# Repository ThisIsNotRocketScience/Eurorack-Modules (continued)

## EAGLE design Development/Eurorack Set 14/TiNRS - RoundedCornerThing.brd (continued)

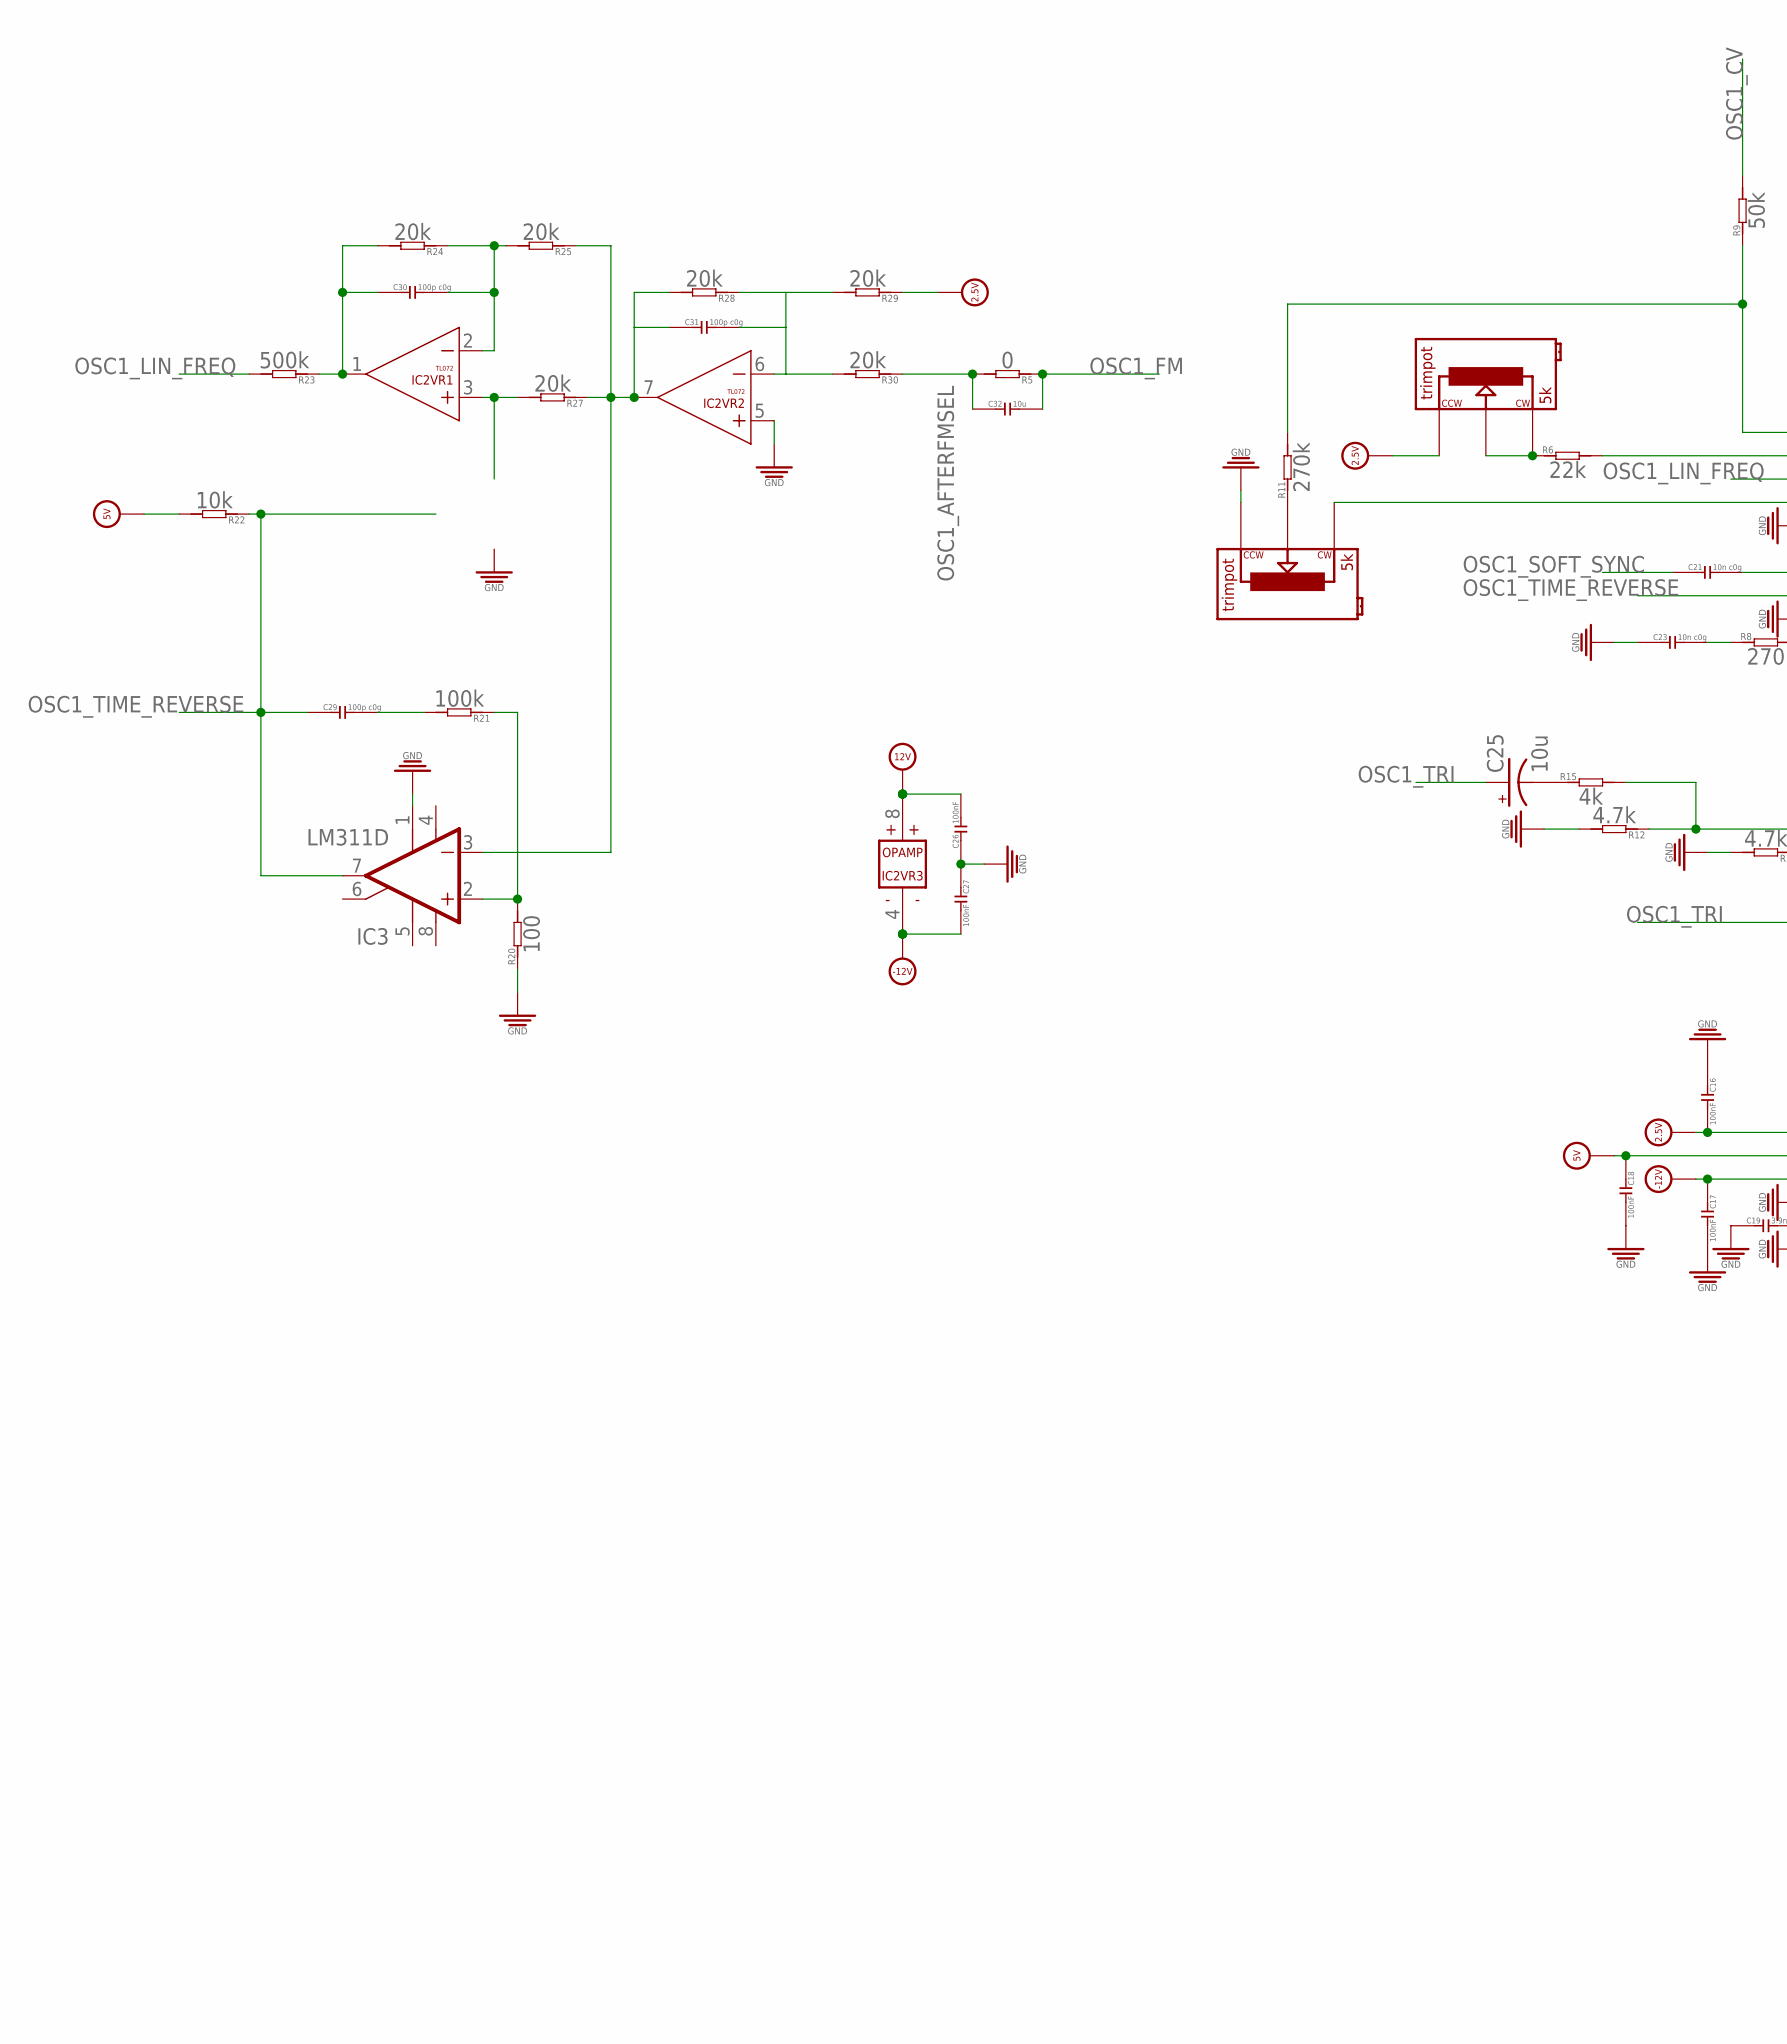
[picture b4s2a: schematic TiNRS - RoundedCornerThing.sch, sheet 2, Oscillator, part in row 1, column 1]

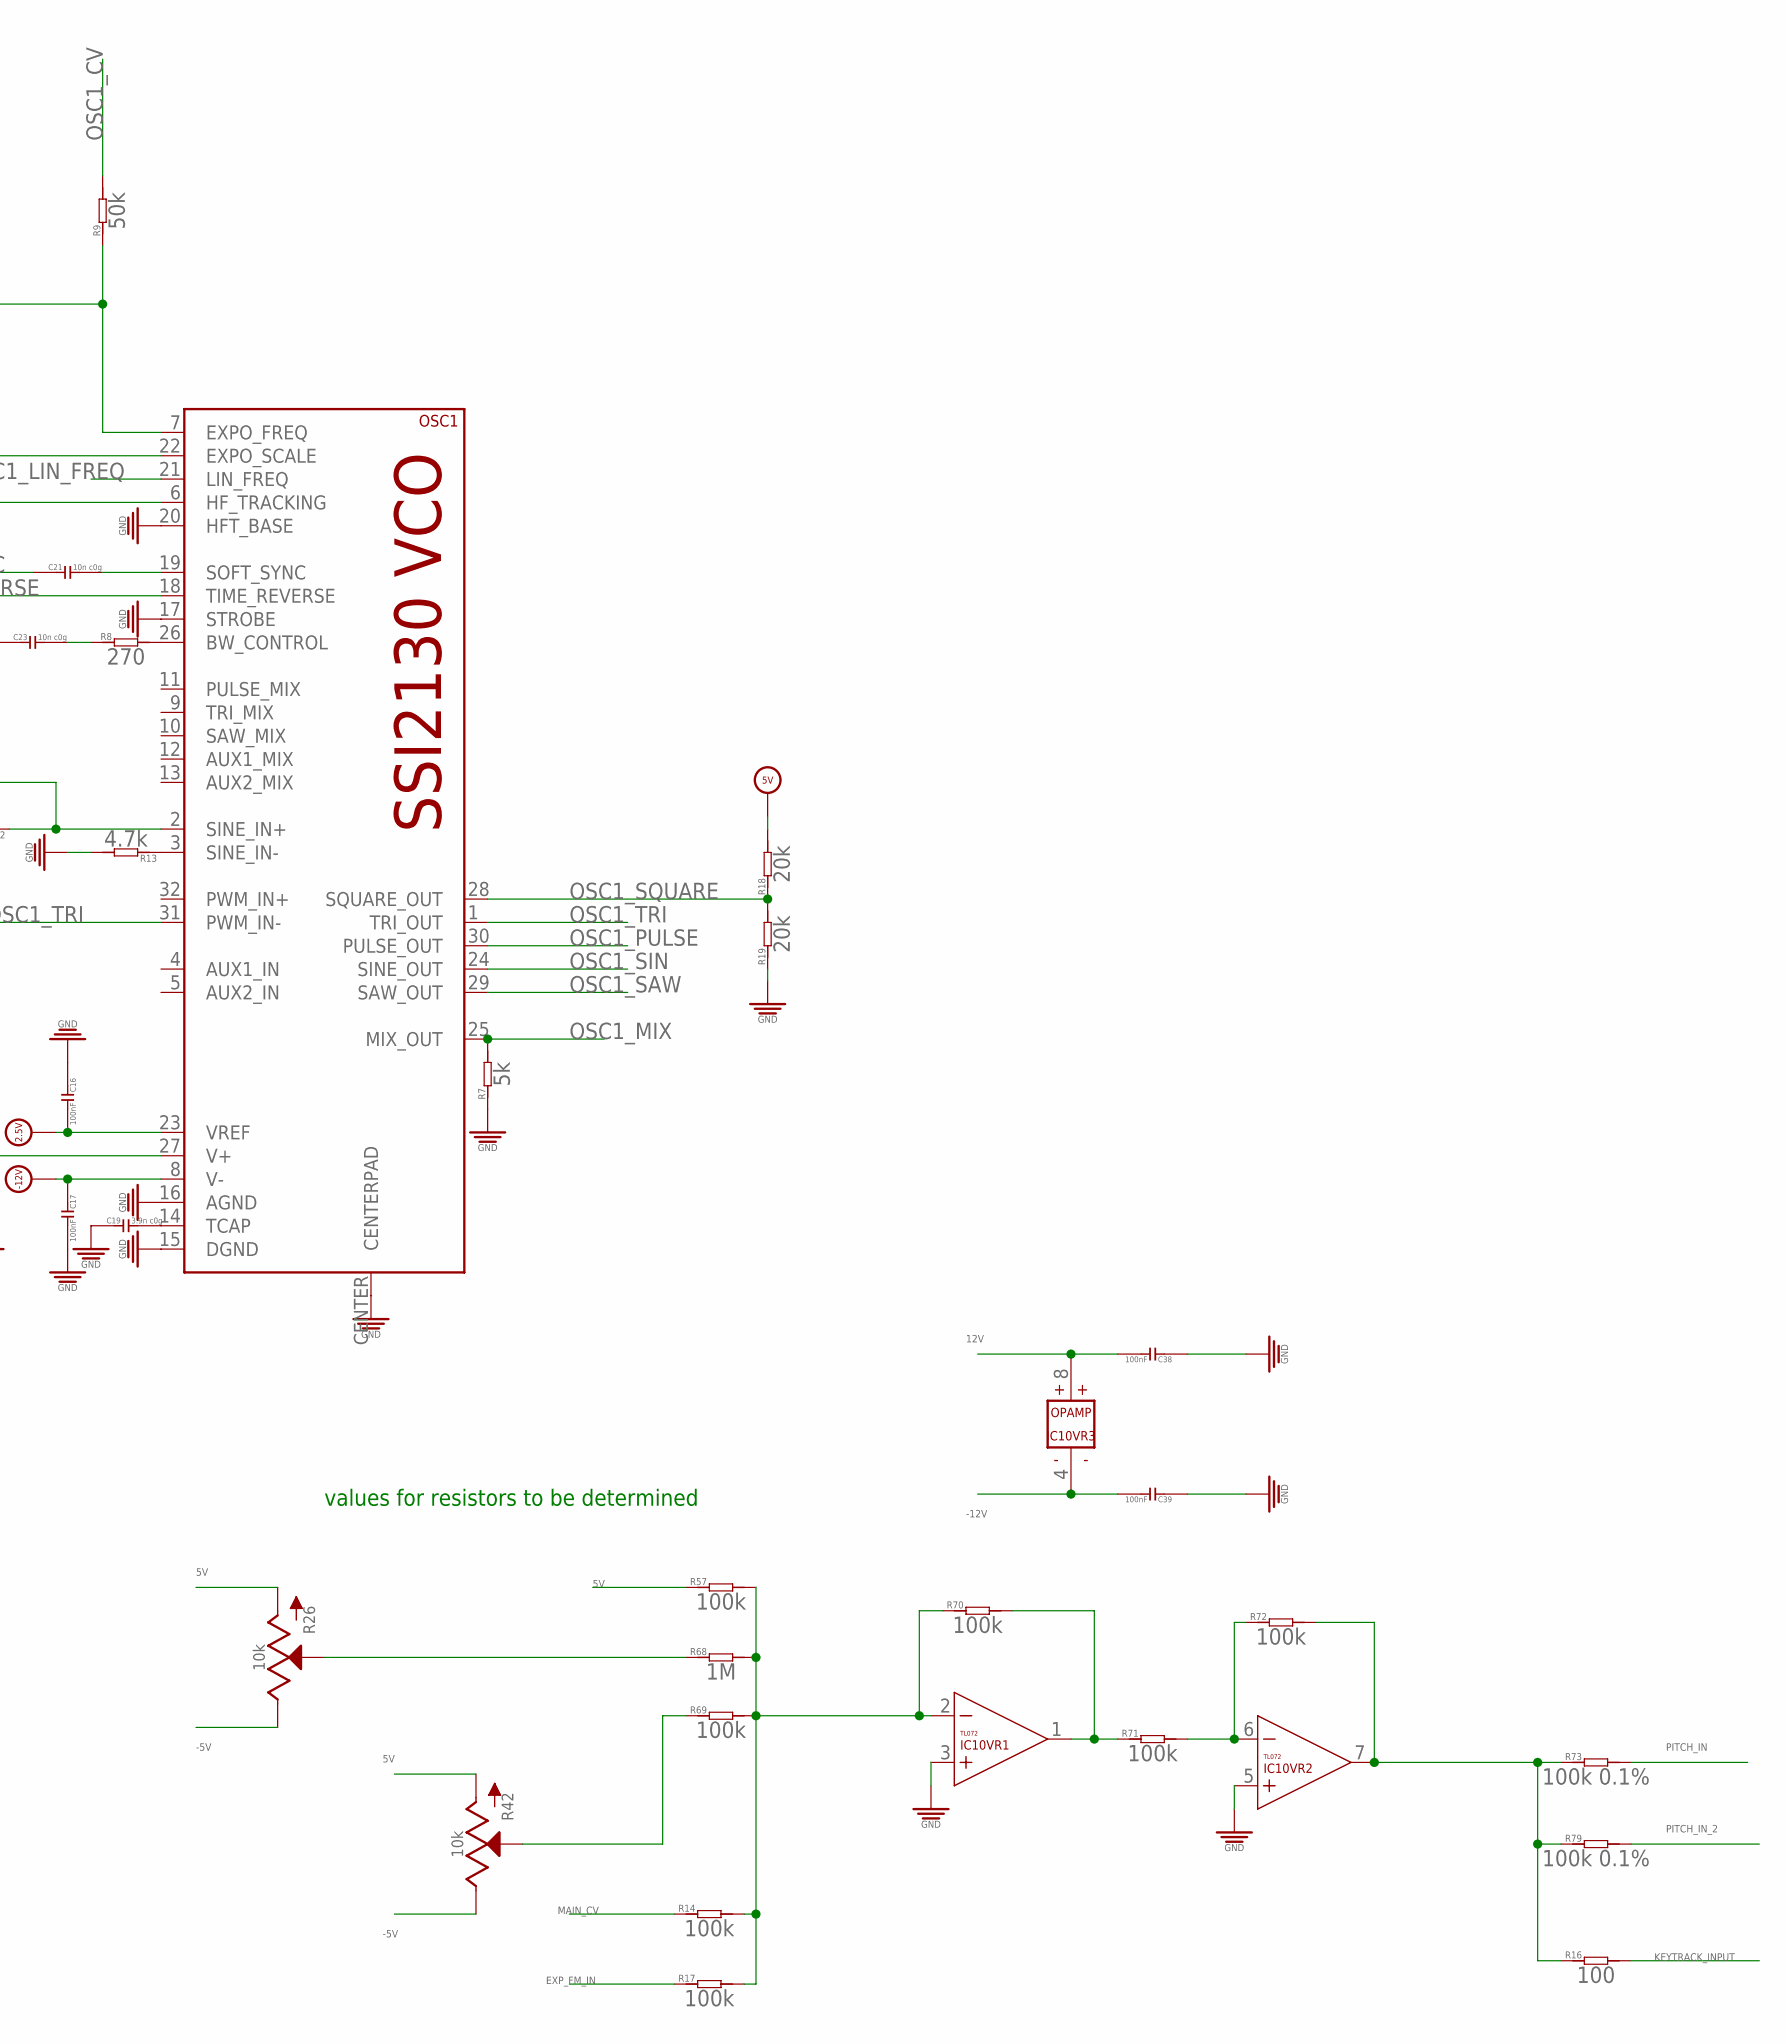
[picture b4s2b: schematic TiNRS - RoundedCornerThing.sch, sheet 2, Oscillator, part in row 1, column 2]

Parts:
C16, C17, C18, C26, C27, C38, C39: 100nF; C0603
C19: 3.9n c0g; C0603
C21, C23: 10n c0g; C0603
C25: 10u; 153CLV-0605
C29, C30, C31: 100p c0g; C0603
C32: 10u; C0603
IC2, IC10: TL072; SO08
IC3: LM311D; SO08
OSC1: SSI2130; QFN32_4X4
R5: 0; R0603
R6: 22k; R0603
R7: 5k; R0603
R8: 270; R0603
R9: 50k; R0603
R10, R189: 5k; TRIMPOT
R11: 270k; R0603
R12, R13: 4.7k; R0603
R14, R17, R21, R57, R69, R70, R71, R72: 100k; R0603
R15: 4k; R0603
R16, R20: 100; R0603
R18, R19, R24, R25, R27, R28, R29, R30: 20k; R0603
R22: 10k; R0603
R23: 500k; R0603
R26, R42: 10k; ALPS_POT_SQUAREHOLES
R68: 1M; R0603
R73, R79: 100k 0.1%; R0603

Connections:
2.5V: C16.2, OSC1.23 (VREF), R29.1, R189.P$1; also elsewhere on the board
5V: C18.1, OSC1.27 (V+), R18.2, R22.2, R26.P$3 (A), R42.P$3 (A), R57.1; also elsewhere on the board
12V: C26.2, C38.2, IC2.8 (V+), IC10.8 (V+); also elsewhere on the board
-5V: R26.P$1 (E), R42.P$1 (E); also elsewhere on the board
-12V: C17.1, C27.2, C39.2, IC2.4 (V-), IC10.4 (V-), OSC1.8 (V-); also elsewhere on the board
EXP_FM_IN: R17.1; also elsewhere on the board
GND: C16.1, C17.2, C18.2, C19.1, C23.1, C26.1, C27.1, C38.1, C39.1, IC2.5 (+IN), IC3.1 (GND), IC10.3 (+IN), IC10.5 (+IN), OSC1.15 (DGND), OSC1.16 (AGND), OSC1.17 (STROBE), OSC1.20 (HFT_BASE), OSC1.CENTER (CENTERPAD), R7.1, R10.P$1, R12.2, R13.2, R19.1, R20.1; also elsewhere on the board
INVERTED_CVSUM: IC10.1 (OUT), R70.2, R71.1
KEYTRACK_INPUT: R16.2; also elsewhere on the board
MAIN_CV: R14.1; also elsewhere on the board
MAIN_CV_SUMLINE: IC10.2 (-IN), R14.2, R17.2, R57.2, R68.2, R69.2, R70.1
MASTER_COARSEPITCH: R42.P$2 (S), R69.1
MASTER_FINEPITCH: R26.P$2 (S), R68.1
unnamed: C19.2, OSC1.14 (TCAP)
unnamed: C21.2, OSC1.19 (SOFT_SYNC)
unnamed: C31.2, IC2.6 (-IN), R30.2
unnamed: OSC1.22 (EXPO_SCALE), R6.2
unnamed: R6.1, R189.P$2, R189.P$3
unnamed: C23.2, R8.1
unnamed: OSC1.26 (BW_CONTROL), R8.2
unnamed: OSC1.7 (EXPO_FREQ), R9.1, R11.2
unnamed: OSC1.6 (HF_TRACKING), R10.P$3
unnamed: R10.P$2, R11.1
unnamed: C25.-, R15.1
unnamed: C30.1, IC2.1 (OUT), R23.1, R24.2
unnamed: OSC1.2 (SINE_IN+), R12.1, R15.2
unnamed: OSC1.3 (SINE_IN-), R13.1
unnamed: C30.2, IC2.2 (-IN), R24.1, R25.2
unnamed: C31.1, IC2.7 (OUT), IC3.3 (-IN), R25.1, R27.1, R28.2
unnamed: IC2.3 (+IN), R27.2
unnamed: R28.1, R29.2
unnamed: IC3.2 (+IN), R20.2, R21.1
unnamed: C29.2, R21.2
OSC1_AFTERFMSEL: C32.1, R5.2, R30.1
OSC1_CV: R9.2
OSC1_FM: C32.2, R5.1
OSC1_LIN_FREQ: OSC1.21 (LIN_FREQ), R23.2
OSC1_MIX: OSC1.25 (MIX_OUT), R7.2
OSC1_PULSE: OSC1.30 (PULSE_OUT)
OSC1_SAW: OSC1.29 (SAW_OUT)
OSC1_SIN: OSC1.24 (SINE_OUT)
OSC1_SOFT_SYNC: C21.1
OSC1_SQUARE: OSC1.28 (SQUARE_OUT), R18.1, R19.2
OSC1_TIME_REVERSE: C29.1, IC3.7 (OUT), OSC1.18 (TIME_REVERSE), R22.1
OSC1_TRI: C25.+, OSC1.1 (TRI_OUT), OSC1.31 (PWM_IN-)
PITCH_IN: R73.2
PITCH_IN_2: R79.2
POSTINVERTED_CVSUM: IC10.6 (-IN), R71.2, R72.1
PRESUMMED_PITCH: IC10.7 (OUT), R16.1, R72.2, R73.1, R79.1
V+: IC3.8 (V+)
V-: IC3.4 (V-)

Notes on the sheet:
values for resistors to be determined

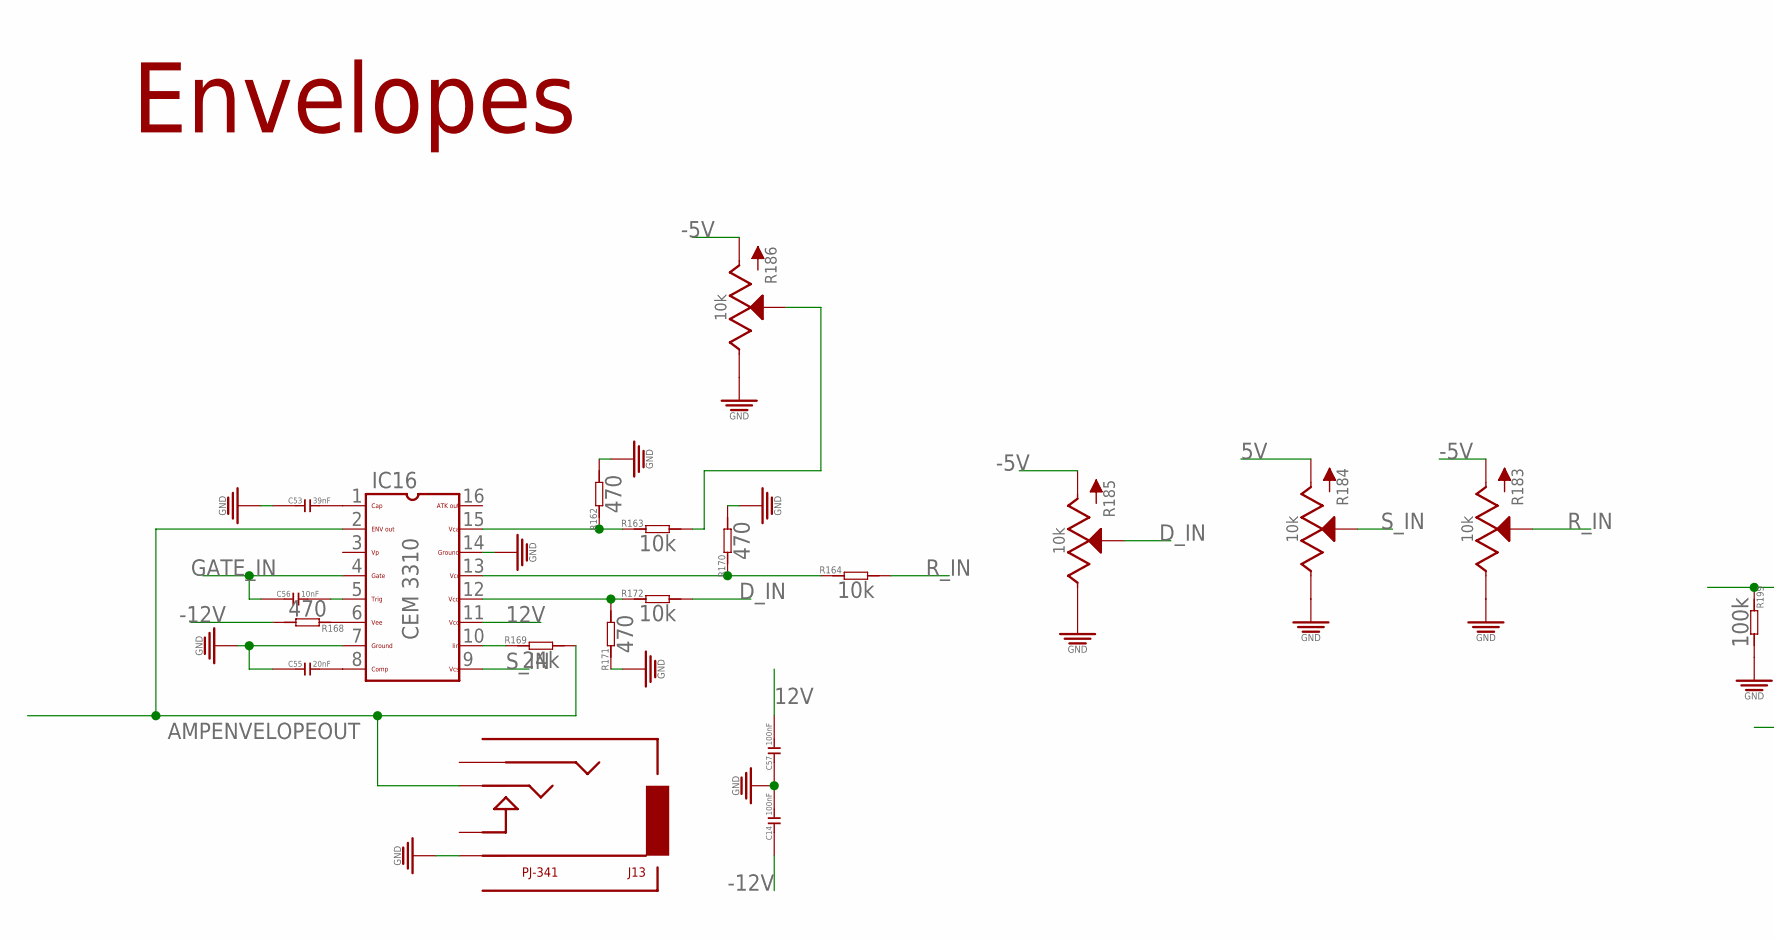
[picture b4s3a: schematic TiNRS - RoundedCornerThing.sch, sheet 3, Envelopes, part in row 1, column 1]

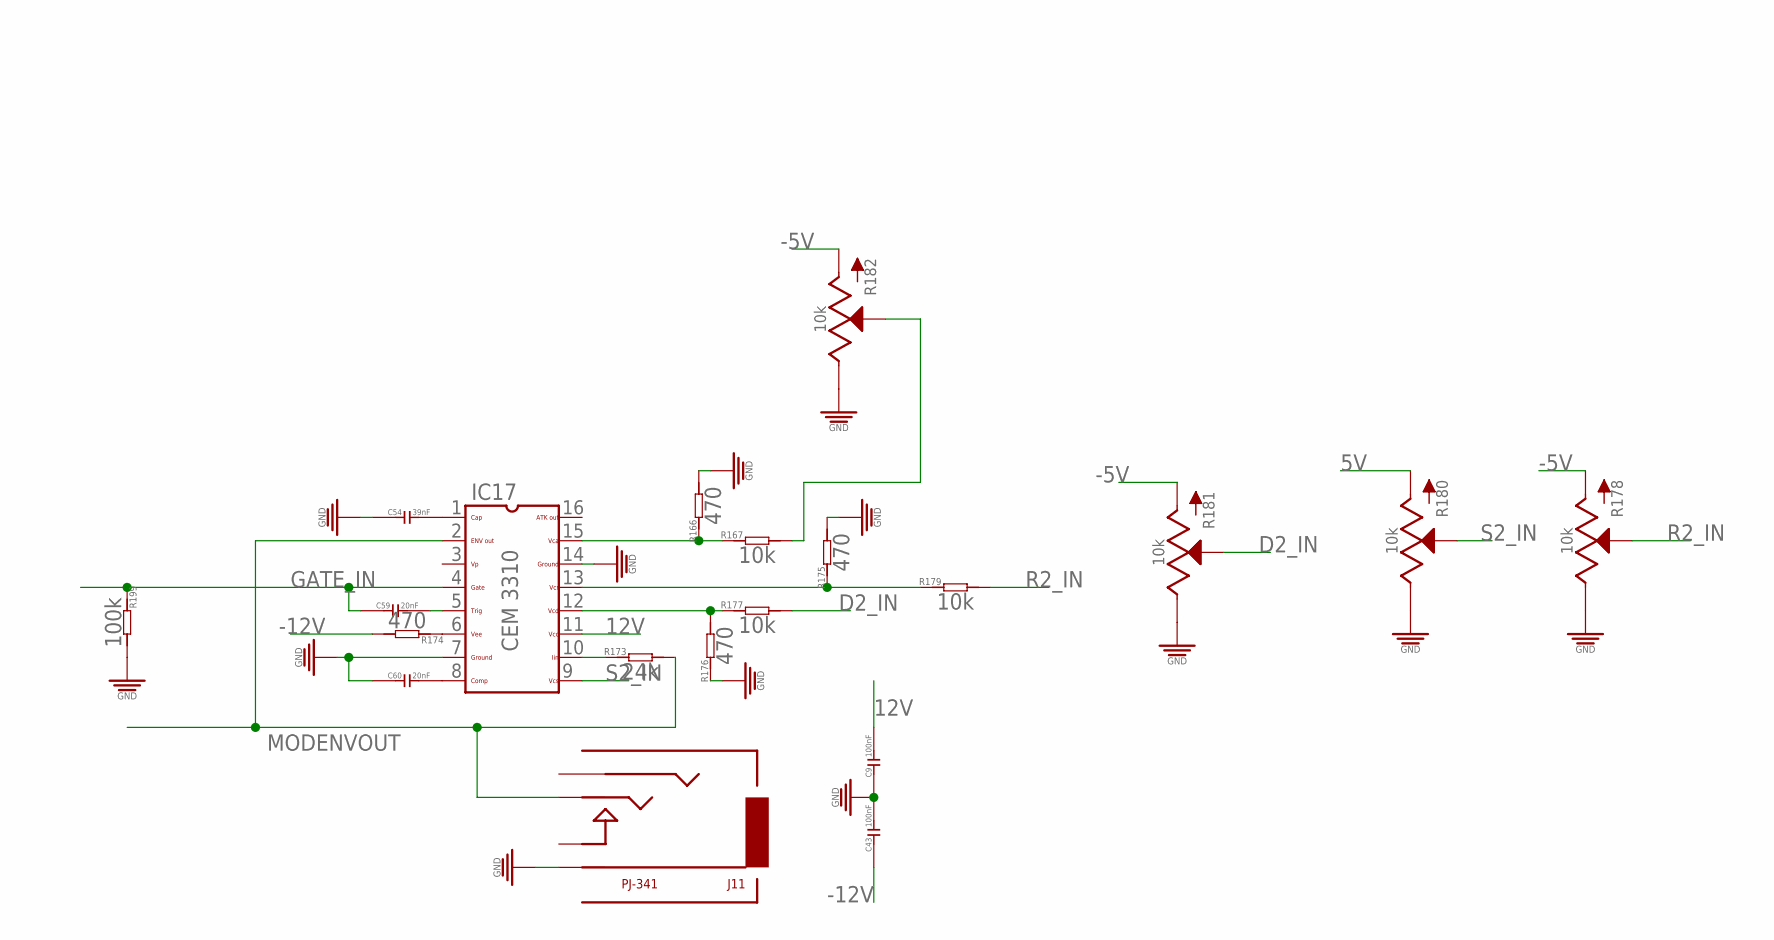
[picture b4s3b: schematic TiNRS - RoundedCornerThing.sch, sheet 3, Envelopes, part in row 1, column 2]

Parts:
C9, C14, C43, C57: 100nF; C0603
C53, C54: 39nF; C0603
C55, C59, C60: 20nF; C0603
C56: 10nF; C0603
IC16, IC17: CEM3310SOIC16; SO16
J11, J13: PJ-341; 3.5MM-JACK-SWITCH-13MM-NOHOLES
R162, R166, R168, R170, R171, R174, R175, R176: 470; R0603
R163, R164, R167, R172, R177, R179: 10k; R0603
R169, R173: 24k; R0603
R178, R180, R181, R182, R183, R184, R185, R186: 10k; ALPS_POT_SQUAREHOLES
R199: 100k; R0603

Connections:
5V: R180.P$3 (A), R184.P$3 (A); also elsewhere on the board
12V: C9.2, C57.2, IC16.11, IC17.11; also elsewhere on the board
-5V: R178.P$3 (A), R181.P$3 (A), R182.P$3 (A), R183.P$3 (A), R185.P$3 (A), R186.P$3 (A); also elsewhere on the board
-12V: C14.1, C43.1, R168.2, R174.2; also elsewhere on the board
A2_IN: R167.2, R182.P$2 (S)
AMPENVELOPEOUT: IC16.2, J13.TIP_B@1 (TIP), J13.TIP_T@3 (TIP), R169.2; also elsewhere on the board
A_IN: R163.2, R186.P$2 (S)
D2_IN: R177.2, R181.P$2 (S)
D_IN: R172.2, R185.P$2 (S)
GATE_IN: C56.1, C59.1, IC16.4, IC17.4, R199.1; also elsewhere on the board
GND: C9.1, C14.2, C43.2, C53.1, C54.1, C55.1, C57.1, C60.1, IC16.7, IC16.14, IC17.7, IC17.14, J11.RING_B@1 (RING), J11.RING_T@3 (RING), J13.RING_B@1 (RING), J13.RING_T@3 (RING), R162.2, R166.2, R170.2, R171.1, R175.2, R176.1, R178.P$1 (E), R180.P$1 (E), R181.P$1 (E), R182.P$1 (E), R183.P$1 (E), R184.P$1 (E), R185.P$1 (E), R186.P$1 (E), R199.2; also elsewhere on the board
MODENVOUT: IC17.2, J11.TIP_B@1 (TIP), J11.TIP_T@3 (TIP), R173.2; also elsewhere on the board
unnamed: IC16.15, R162.1, R163.1
unnamed: IC16.12, R171.2, R172.1
unnamed: IC16.13, R164.1, R170.1
unnamed: C53.2, IC16.1
unnamed: C56.2, IC16.5
unnamed: IC16.6, R168.1
unnamed: C55.2, IC16.8
unnamed: IC16.10, R169.1
unnamed: IC17.15, R166.1, R167.1
unnamed: IC17.12, R176.2, R177.1
unnamed: IC17.13, R175.1, R179.1
unnamed: C59.2, IC17.5
unnamed: IC17.6, R174.1
unnamed: C60.2, IC17.8
unnamed: IC17.10, R173.1
unnamed: C54.2, IC17.1
R2_IN: R178.P$2 (S), R179.2
R_IN: R164.2, R183.P$2 (S)
S2_IN: IC17.9, R180.P$2 (S)
S_IN: IC16.9, R184.P$2 (S)

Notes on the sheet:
Envelopes

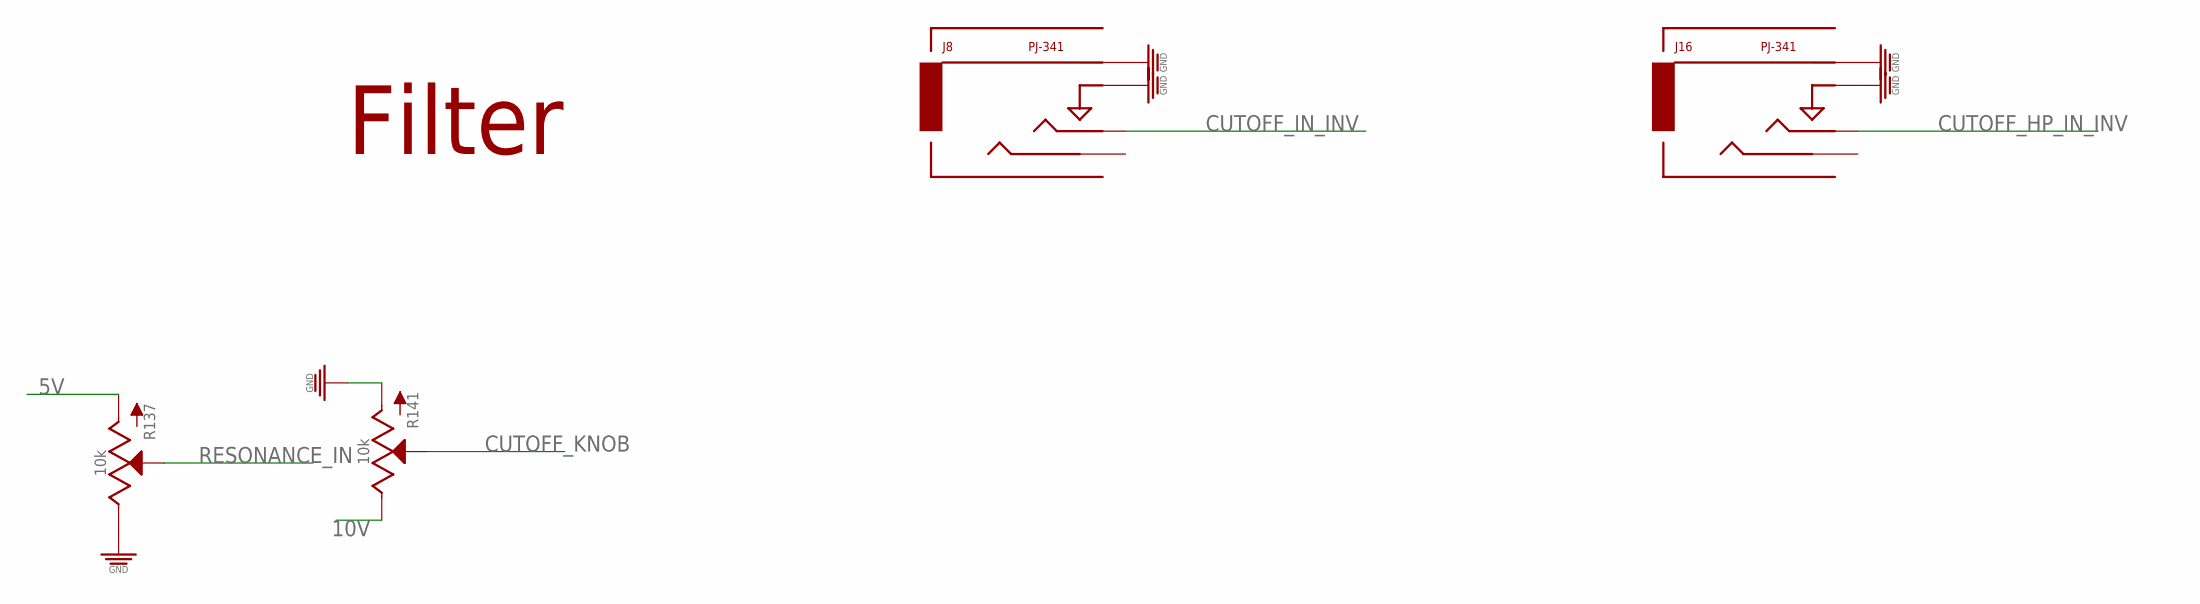
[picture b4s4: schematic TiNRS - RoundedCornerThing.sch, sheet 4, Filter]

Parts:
J8, J16: PJ-341; 3.5MM-JACK-SWITCH-13MM-NOHOLES
R137, R141: 10k; ALPS_POT_SQUAREHOLES

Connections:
5V: R137.P$3 (A); also elsewhere on the board
10V: R141.P$1 (E); also elsewhere on the board
CUTOFF_HP_IN_INV: J16.TIP_B@1 (TIP), J16.TIP_T@3 (TIP); also elsewhere on the board
CUTOFF_IN_INV: J8.TIP_B@1 (TIP), J8.TIP_T@3 (TIP); also elsewhere on the board
CUTOFF_KNOB: R141.P$2 (S)
GND: J8.RING_B@1 (RING), J8.RING_T@3 (RING), J8.SWITCH_B@1 (SWITCH), J8.SWITCH_T@3 (SWITCH), J16.RING_B@1 (RING), J16.RING_T@3 (RING), J16.SWITCH_B@1 (SWITCH), J16.SWITCH_T@3 (SWITCH), R137.P$1 (E), R141.P$3 (A); also elsewhere on the board
RESONANCE_IN: R137.P$2 (S)

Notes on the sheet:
Filter

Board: 2 copper layers, 183 parts (7 on the bottom side), 113 nets, no tracks yet.

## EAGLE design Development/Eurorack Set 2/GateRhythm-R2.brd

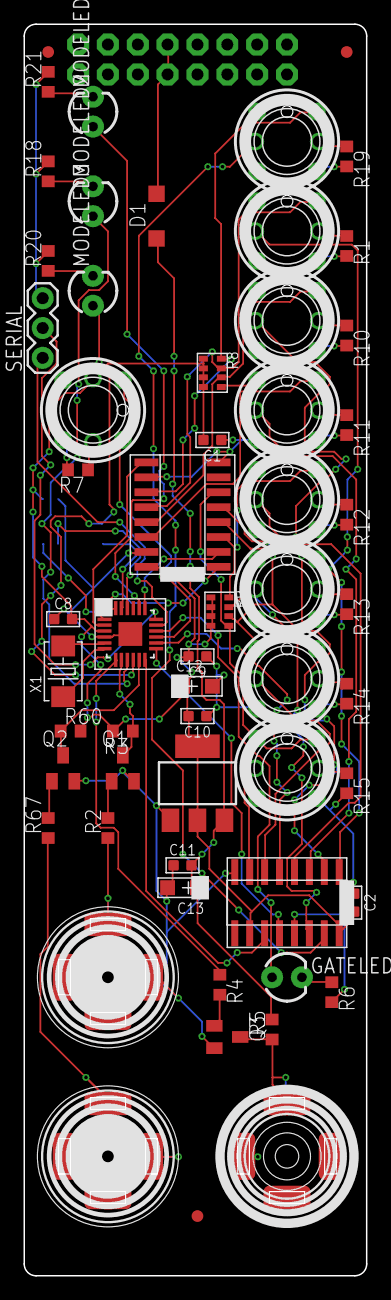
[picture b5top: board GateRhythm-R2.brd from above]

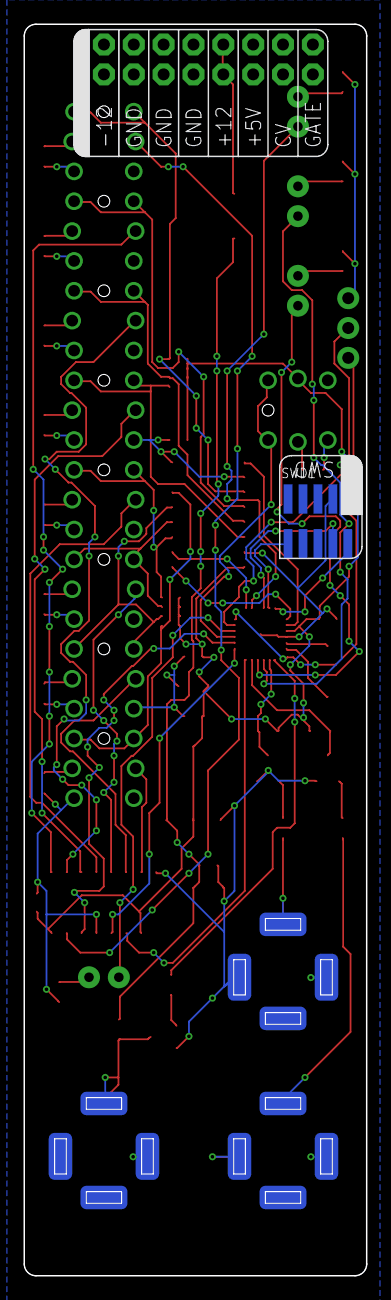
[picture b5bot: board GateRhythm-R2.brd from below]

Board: 2 copper layers, 29.1 x 106.5 mm, 61 parts (2 on the bottom side), 60 nets.

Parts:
B1, B2, B3, B4, B5, B6, B7, B8, B9: SWITCH_W_LED_PB6149L-X-102WHITE; PB6149L
C1, C2, C11: 100Nf; C0603
C8, C10: 100nF; C0603
C9: 1uF; C0603
C12: 10uF; AVX-A
C13: 10Uf; AVX-A
CLOCK: Clock; 3.5MM-JACK-SWITCH-13MM-INPUT
D1: 1N5819HW; SOD123
GATE: Gate; 3.5MM-JACK-SWITCH-13MM-OUTPUT
GATELED: LED3MM
IC1: LD1117AS33TR; SOT223
IC2: IC_74HC595-SOIC-16; SOIC-16
IC3: 74AC165D; SO16
MODELED1, MODELED2, MODELED3: LED3MM
Q1, Q2, Q3: MMBT3904; SOT23-BEC
R1, R6, R7, R10, R11, R12, R13, R14, R15, R18, R19, R20, R21: 120; R0603
R2, R4, R67: 100k; R0603
R3, R5, R60: 10k; R0603
R8, R9: 10k; R1206-8
RESET: Reset; 3.5MM-JACK-SWITCH-13MM-INPUT
SERIAL: 1X03
SWD1: CORTEX_SWD; M50-3600542
U1: MKL02Z32VFK4; QFN50P400X400X100-25N
U$1: POWER; POWER_16
U$2: EURORACK_PCB6HP; EURORACK6HPPCB
U$3, U$4, U$5: FIDUCIAL; FIDUCIAL_1MM
X1: CRYSTAL-0500290P1; 2P-SMD-5.0X3.2

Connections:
3.3V: B9.LEDPOS, C1.2, C2.2, C8.2, C9.2, C10.2, C12.+, IC1.2, IC1.4, IC2.10, IC2.16, IC3.16, R3.2, R8.1, R8.2, R8.3, R8.4, R9.1, R9.2, R9.3, R9.4, R60.2, SWD1.1, U1.3
12V: C11.2, C13.+, D1.C, IC1.3, R5.2
BUTTON1: B1.1, B1.2, IC3.11, R8.8
BUTTON2: B2.1, B2.2, IC3.12, R8.7
BUTTON3: B3.1, B3.2, IC3.13, R8.6
BUTTON4: B4.1, B4.2, IC3.14, R8.5
BUTTON5: B5.1, B5.2, IC3.3, R9.8
BUTTON6: B6.1, B6.2, IC3.4, R9.7
BUTTON7: B7.1, B7.2, IC3.5, R9.6
BUTTON8: B8.1, B8.2, IC3.6, R9.5
BUTTONCLOCK: IC3.2, U1.19
BUTTONDAT: IC3.9, U1.2
BUTTONLATCH: IC3.1, U1.1
CLOCK: Q2.C, R60.1, U1.11
GATELED: GATELED.A, U1.16
GND: B1.3, B1.4, B2.3, B2.4, B3.3, B3.4, B4.3, B4.4, B5.3, B5.4, B6.3, B6.4, B7.3, B7.4, B8.3, B8.4, B9.3, B9.4, C1.1, C2.1, C8.1, C9.1, C10.1, C11.1, C12.-, C13.-, CLOCK.RING@1, CLOCK.RING@2, CLOCK.SWITCH@1, CLOCK.SWITCH@2, GATE.RING@1, GATE.RING@2, IC1.1, IC2.8, IC2.13, IC3.8, IC3.10, IC3.15, Q1.E, Q2.E, Q3.E, R1.2, R6.2, R7.2, R10.2, R11.2, R12.2, R13.2, R14.2, R15.2, R18.2, R19.2, R20.2, R21.2, RESET.RING@1, RESET.RING@2, RESET.SWITCH@1, RESET.SWITCH@2, SERIAL.3, SWD1.3, SWD1.5, U1.4, U1.25, U$1.3, U$1.4, U$1.5, U$1.6, U$1.7, U$1.8
LEDB1: B1.LEDPOS, IC2.15
LEDB2: B2.LEDPOS, IC2.1
LEDB3: B3.LEDPOS, IC2.2
LEDB4: B4.LEDPOS, IC2.3
LEDB5: B5.LEDPOS, IC2.4
LEDB6: B6.LEDPOS, IC2.5
LEDB7: B7.LEDPOS, IC2.6
LEDB8: B8.LEDPOS, IC2.7
LEDCLOCK: IC2.11, U1.12
LEDDAT: IC2.14, U1.14
LEDLATCH: IC2.12, U1.13
MODEBUTTON: B9.1, B9.2, U1.15
MODELED1: MODELED1.A, U1.20
MODELED2: MODELED2.A, U1.9
MODELED3: MODELED3.A, U1.10
unnamed: U1.5, X1.2
unnamed: U1.6, X1.1
unnamed: B2.LEDNEG, R1.1
unnamed: Q1.B, R2.2
unnamed: SWD1.4, U1.22
unnamed: R2.1, RESET.TIP@1, RESET.TIP@2
unnamed: SWD1.2, U1.24
unnamed: B3.LEDNEG, R10.1
unnamed: Q3.B, R4.2
unnamed: GATELED.K, R6.1
unnamed: B9.LEDNEG, R7.1
unnamed: D1.A, U$1.9, U$1.10
unnamed: B1.LEDNEG, R19.1
unnamed: MODELED2.K, R18.1
unnamed: MODELED3.K, R20.1
unnamed: MODELED1.K, R21.1
unnamed: B4.LEDNEG, R11.1
unnamed: B5.LEDNEG, R12.1
unnamed: B6.LEDNEG, R13.1
unnamed: B7.LEDNEG, R14.1
unnamed: B8.LEDNEG, R15.1
unnamed: CLOCK.TIP@1, CLOCK.TIP@2, R67.1
unnamed: Q2.B, R67.2
PTA1: SWD1.10, U1.23
RESET: Q1.C, R3.1, U1.8
RX: SERIAL.2, U1.18
TRIG: R4.1, U1.7
TRIGGEROUT: GATE.TIP@1, GATE.TIP@2, Q3.C, R5.1
TX: SERIAL.1, U1.17

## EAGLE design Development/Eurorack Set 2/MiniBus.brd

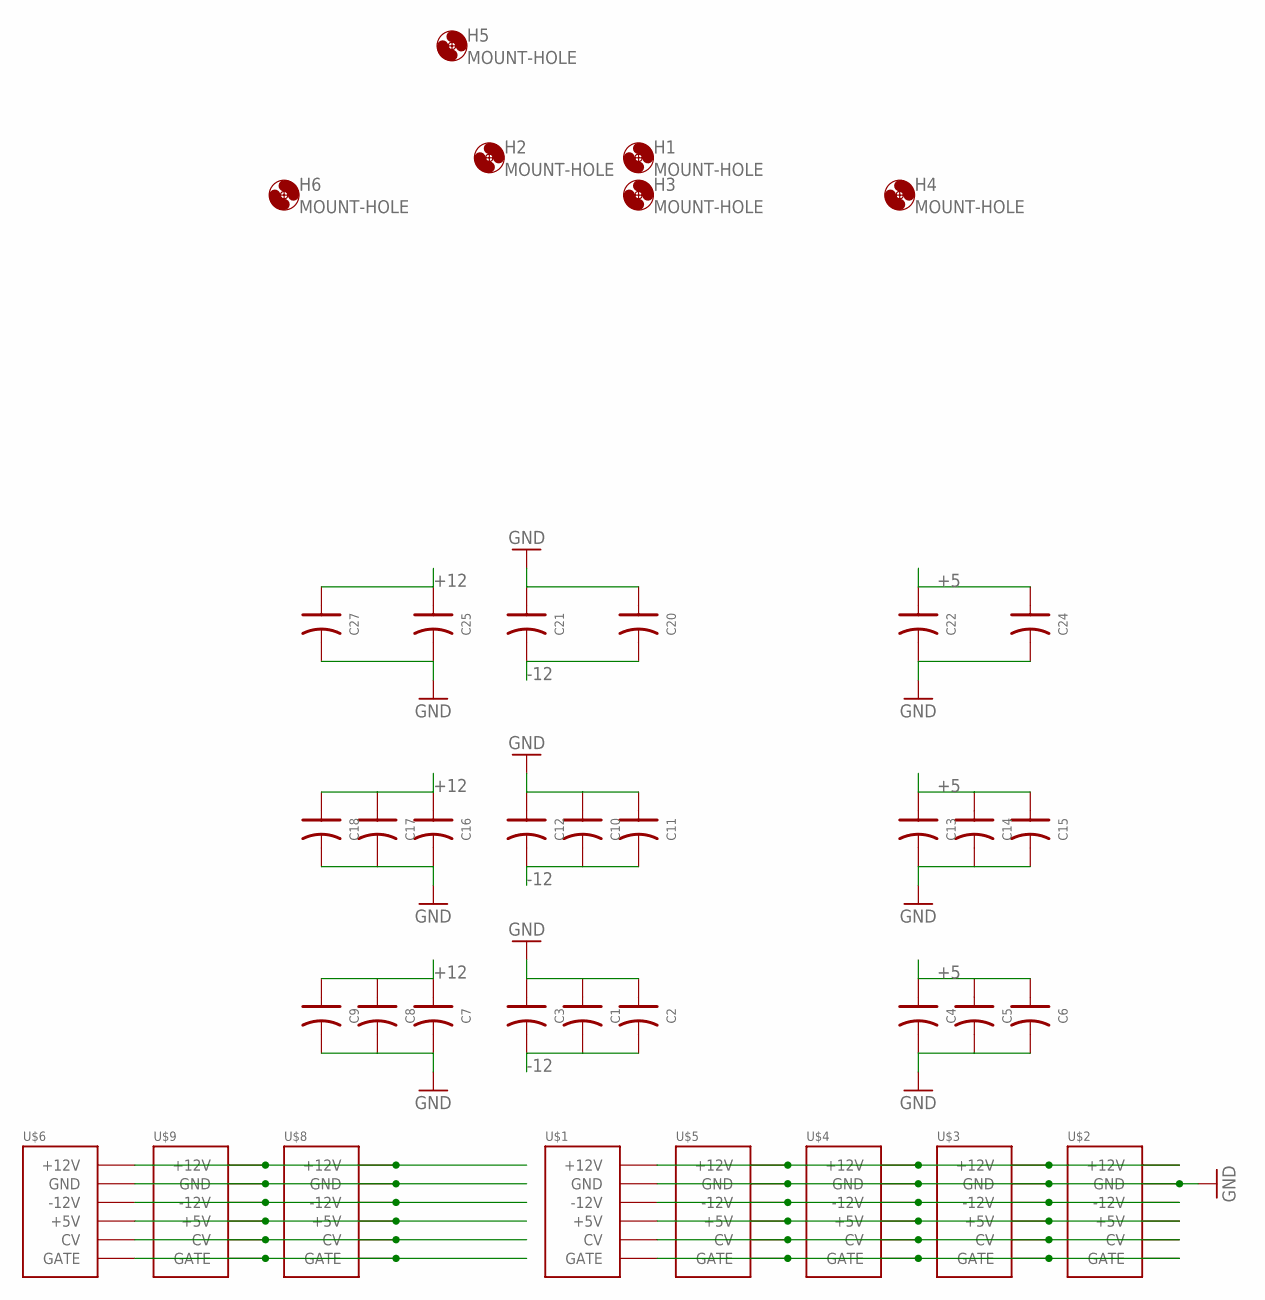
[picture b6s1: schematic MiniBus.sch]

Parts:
C1, C2, C3, C4, C5, C6, C7, C8, C9, C10, C11, C12, C13, C14, C15, C16, C17, C18, C20, C21, C22, C24, C25, C27: C-POLAR-A; AVX-A
H1, H2, H3, H4, H5, H6: MOUNT-HOLE; 3.2-NOMARKINGS-SMALLSAFEZONE
U$1, U$2, U$3, U$4, U$5, U$6, U$8, U$9: POWER; POWER_16

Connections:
+5: C4.+ (1), C5.+ (1), C6.+ (1), C13.+ (1), C14.+ (1), C15.+ (1), C22.+ (1), C24.+ (1), U$1.11 (+5V), U$1.12 (+5V), U$2.11 (+5V), U$2.12 (+5V), U$3.11 (+5V), U$3.12 (+5V), U$4.11 (+5V), U$4.12 (+5V), U$5.11 (+5V), U$5.12 (+5V), U$6.11 (+5V), U$6.12 (+5V), U$8.11 (+5V), U$8.12 (+5V), U$9.11 (+5V), U$9.12 (+5V)
+12: C7.+ (1), C8.+ (1), C9.+ (1), C16.+ (1), C17.+ (1), C18.+ (1), C25.+ (1), C27.+ (1), U$1.9 (+12V), U$1.10 (+12V), U$2.9 (+12V), U$2.10 (+12V), U$3.9 (+12V), U$3.10 (+12V), U$4.9 (+12V), U$4.10 (+12V), U$5.9 (+12V), U$5.10 (+12V), U$6.9 (+12V), U$6.10 (+12V), U$8.9 (+12V), U$8.10 (+12V), U$9.9 (+12V), U$9.10 (+12V)
-12: C1.- (2), C2.- (2), C3.- (2), C10.- (2), C11.- (2), C12.- (2), C20.- (2), C21.- (2), U$1.1 (-12V), U$1.2 (-12V), U$2.1 (-12V), U$2.2 (-12V), U$3.1 (-12V), U$3.2 (-12V), U$4.1 (-12V), U$4.2 (-12V), U$5.1 (-12V), U$5.2 (-12V), U$6.1 (-12V), U$6.2 (-12V), U$8.1 (-12V), U$8.2 (-12V), U$9.1 (-12V), U$9.2 (-12V)
CV: U$1.13 (CV), U$1.14 (CV), U$2.13 (CV), U$2.14 (CV), U$3.13 (CV), U$3.14 (CV), U$4.13 (CV), U$4.14 (CV), U$5.13 (CV), U$5.14 (CV), U$6.13 (CV), U$6.14 (CV), U$8.13 (CV), U$8.14 (CV), U$9.13 (CV), U$9.14 (CV)
GATE: U$1.15 (GATE), U$1.16 (GATE), U$2.15 (GATE), U$2.16 (GATE), U$3.15 (GATE), U$3.16 (GATE), U$4.15 (GATE), U$4.16 (GATE), U$5.15 (GATE), U$5.16 (GATE), U$6.15 (GATE), U$6.16 (GATE), U$8.15 (GATE), U$8.16 (GATE), U$9.15 (GATE), U$9.16 (GATE)
GND: C1.+ (1), C2.+ (1), C3.+ (1), C4.- (2), C5.- (2), C6.- (2), C7.- (2), C8.- (2), C9.- (2), C10.+ (1), C11.+ (1), C12.+ (1), C13.- (2), C14.- (2), C15.- (2), C16.- (2), C17.- (2), C18.- (2), C20.+ (1), C21.+ (1), C22.- (2), C24.- (2), C25.- (2), C27.- (2), U$1.3 (GND), U$1.4 (GND), U$1.5 (GND), U$1.6 (GND), U$1.7 (GND), U$1.8 (GND), U$2.3 (GND), U$2.4 (GND), U$2.5 (GND), U$2.6 (GND), U$2.7 (GND), U$2.8 (GND), U$3.3 (GND), U$3.4 (GND), U$3.5 (GND), U$3.6 (GND), U$3.7 (GND), U$3.8 (GND), U$4.3 (GND), U$4.4 (GND), U$4.5 (GND), U$4.6 (GND), U$4.7 (GND), U$4.8 (GND), U$5.3 (GND), U$5.4 (GND), U$5.5 (GND), U$5.6 (GND), U$5.7 (GND), U$5.8 (GND), U$6.3 (GND), U$6.4 (GND), U$6.5 (GND), U$6.6 (GND), U$6.7 (GND), U$6.8 (GND), U$8.3 (GND), U$8.4 (GND), U$8.5 (GND), U$8.6 (GND), U$8.7 (GND), U$8.8 (GND), U$9.3 (GND), U$9.4 (GND), U$9.5 (GND), U$9.6 (GND), U$9.7 (GND), U$9.8 (GND)

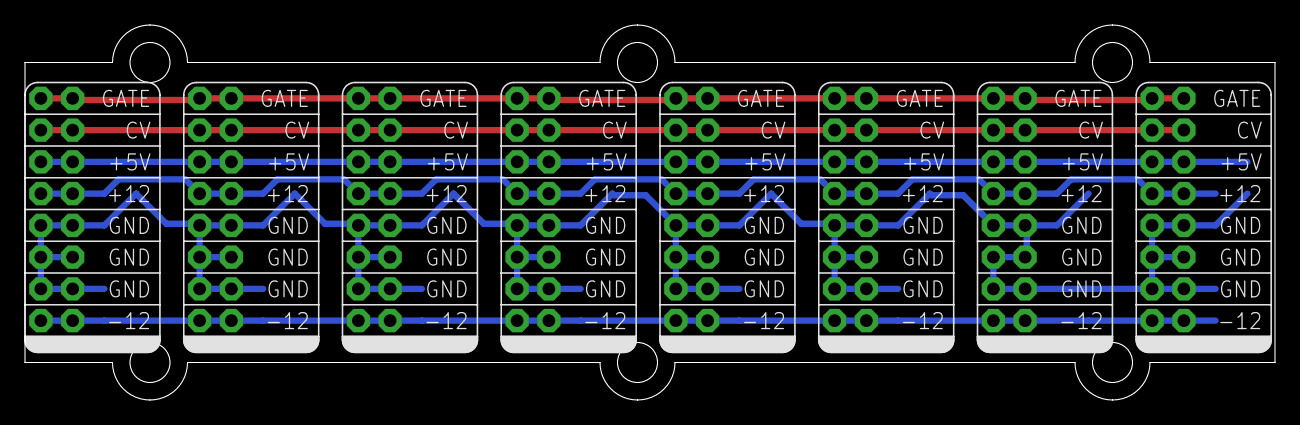
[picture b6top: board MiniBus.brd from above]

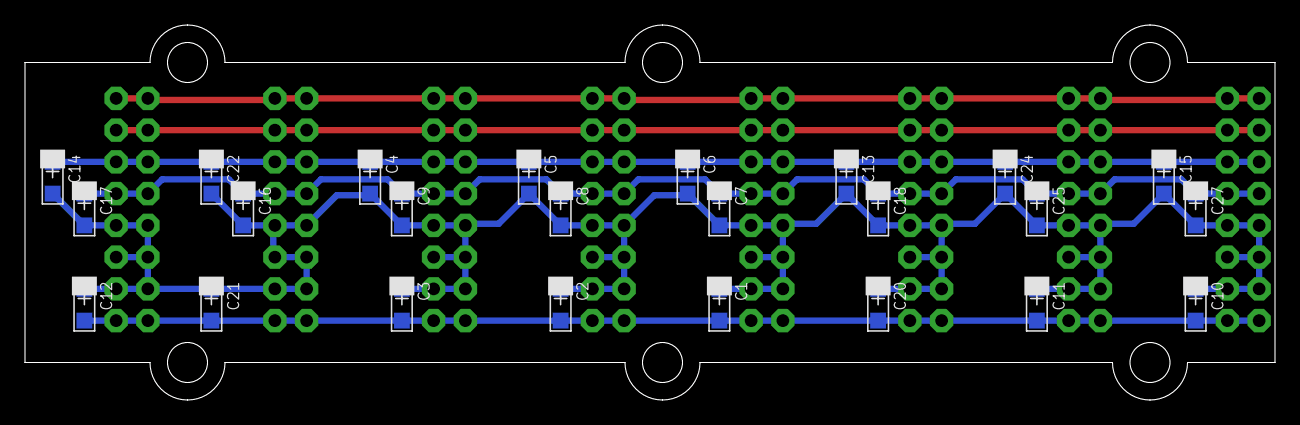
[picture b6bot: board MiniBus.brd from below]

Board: 2 copper layers, 100.0 x 30.0 mm, 38 parts (24 on the bottom side), 6 nets.
